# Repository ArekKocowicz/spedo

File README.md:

# spedo
Bicycle display supplied from dynamo hub (no speed sensor needed, no battery needed)

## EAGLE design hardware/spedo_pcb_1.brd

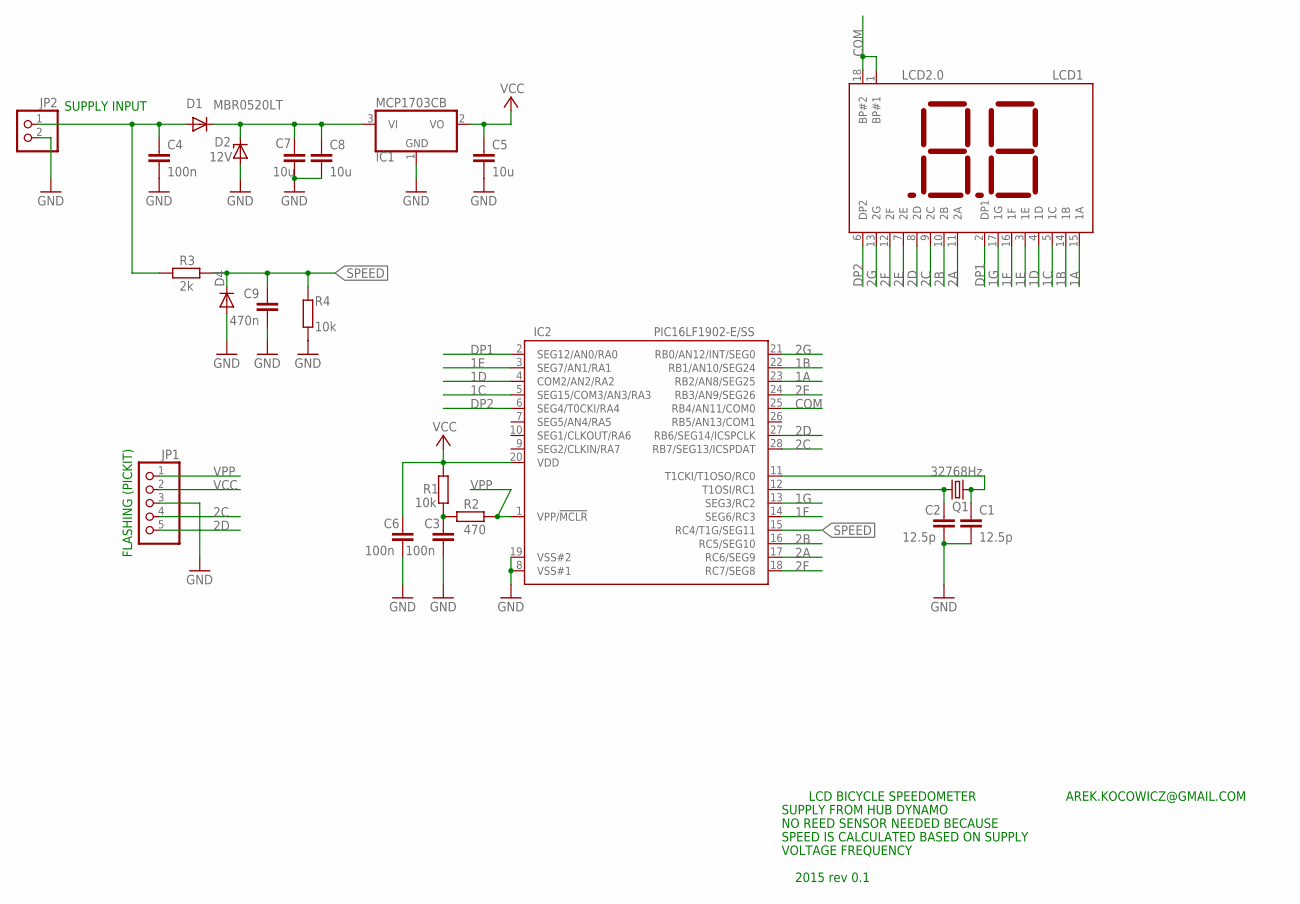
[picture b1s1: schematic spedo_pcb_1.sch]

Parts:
C1, C2: 12.5p; C0603K
C3, C4, C6: 100n; C0603K
C5, C7, C8: 10u; C0805K
C9: 470n; C0603K
D1: MBR0520LT; SOD123
D2: 12V; SOD80C
D4: DIODE-SOD323-W; SOD323-W
IC1: MCP1703CB; SOT23
IC2: PIC16LF1902-E/SS; SSOP28
JP1: PINHD-1X5/90; 1X05/90
JP2: PINHD-1X2; 1X02
LCD1: LCD2.0
Q1: 32768Hz; TC26H
R1, R4: 10k; R0603
R2: 470; R0603
R3: 2k; R0603

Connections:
1A: IC2.23 (RB2/AN8/SEG25), LCD1.15 (1A)
1B: IC2.22 (RB1/AN10/SEG24), LCD1.14 (1B)
1C: IC2.5 (SEG15/COM3/AN3/RA3), LCD1.5 (1C)
1D: IC2.4 (COM2/AN2/RA2), LCD1.4 (1D)
1E: IC2.3 (SEG7/AN1/RA1), LCD1.3 (1E)
1F: IC2.14 (SEG6/RC3), LCD1.16 (1F)
1G: IC2.13 (SEG3/RC2), LCD1.17 (1G)
2A: IC2.17 (RC6/SEG9), LCD1.11 (2A)
2B: IC2.16 (RC5/SEG10), LCD1.10 (2B)
2C: IC2.28 (RB7/SEG13/ICSPDAT), JP1.4, LCD1.9 (2C)
2D: IC2.27 (RB6/SEG14/ICSPCLK), JP1.5, LCD1.8 (2D)
2E: IC2.24 (RB3/AN9/SEG26), LCD1.7 (2E)
2F: IC2.18 (RC7/SEG8), LCD1.12 (2F)
2G: IC2.21 (RB0/AN12/INT/SEG0), LCD1.13 (2G)
COM: IC2.25 (RB4/AN11/COM0), LCD1.1 (BP#1), LCD1.18 (BP#2)
DP1: IC2.2 (SEG12/AN0/RA0), LCD1.2 (DP1)
DP2: IC2.6 (SEG4/T0CKI/RA4), LCD1.6 (DP2)
GND: C1.2, C2.2, C3.2, C4.2, C5.2, C6.2, C7.2, C8.2, C9.2, D2.A, D4.A, IC1.1 (GND), IC2.8 (VSS#1), IC2.19 (VSS#2), JP1.3, JP2.2, R4.2
unnamed: C1.1, IC2.11 (T1CKI/T1OSO/RC0), Q1.2
unnamed: C2.1, IC2.12 (T1OSI/RC1), Q1.1
unnamed: C4.1, D1.A, JP2.1, R3.1
unnamed: C3.1, R1.2, R2.1
unnamed: C7.1, C8.1, D1.C, D2.C, IC1.3 (VI)
SPEED: C9.1, D4.C, IC2.15 (RC4/T1G/SEG11), R3.2, R4.1
VCC: C5.1, C6.1, IC1.2 (VO), IC2.20 (VDD), JP1.2, R1.1
VPP: IC2.1 (VPP/!MCLR), JP1.1, R2.2

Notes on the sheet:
AREK.KOCOWICZ@GMAIL.COM
LCD BICYCLE SPEEDOMETER
SUPPLY FROM HUB DYNAMO
NO REED SENSOR NEEDED BECAUSE
SPEED IS CALCULATED BASED ON SUPPLY
VOLTAGE FREQUENCY
FLASHING (PICKIT)
SUPPLY INPUT
2015 rev 0.1

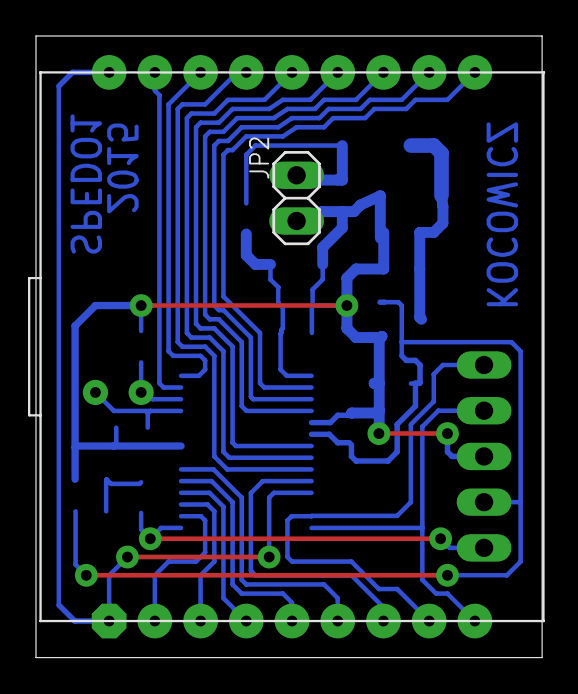
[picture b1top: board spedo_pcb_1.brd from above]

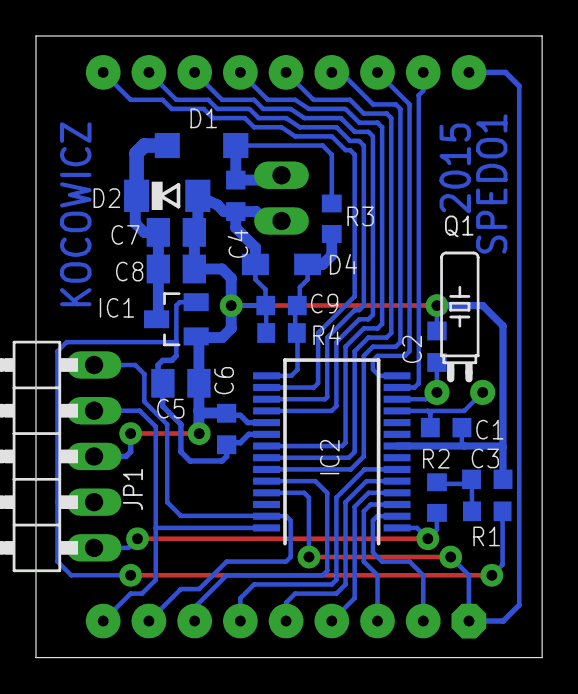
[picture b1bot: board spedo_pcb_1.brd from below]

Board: 2 copper layers, 28.1 x 34.5 mm, 22 parts (20 on the bottom side), 26 nets.

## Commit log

2015-02-12 Added option to display -- when no speed info is available yet.
2015-02-16 Added circuit, PCB and gerber files
2015-02-22 Changed the way LCD display is controlled. In the first prototype SEG_A was controlled from the same bit in DATAn register. This was easier to code but such a PCB layout was not possible to keep on a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
2015-02-23 Further rework on LCD. I added neatly packed dot status as a input for the lcdDisplay function. LCD functions are now in a separate file.
2015-03-02 Added lcdDisplayAll which takes a number as an argument and displays it on two digits if no blanking selected in argument. If blanking selected then display shows --. Leading zero is blanked.
2015-05-14 fixed LCD pinout, added speed calculation and limiting of displayed values to 99
2015-05-15 this software version has been flashed to a prototype mounted on a bicycle.
2015-12-30 this version supports storing wheel circumference in flash memory.
2016-01-28 Added checking OERR and FERR bits when EUSART bit received
